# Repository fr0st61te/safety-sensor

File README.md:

# safety-sensor

This is a primitive safety/tamper sensor based on STM8 and VCNL3020 proximity sensor with simple backup power mechanism. STM8 application saves state
of interrupt and store it in flash memory, blinks when interrupt occurs.

# Schematic

# PCB

# Physical examples

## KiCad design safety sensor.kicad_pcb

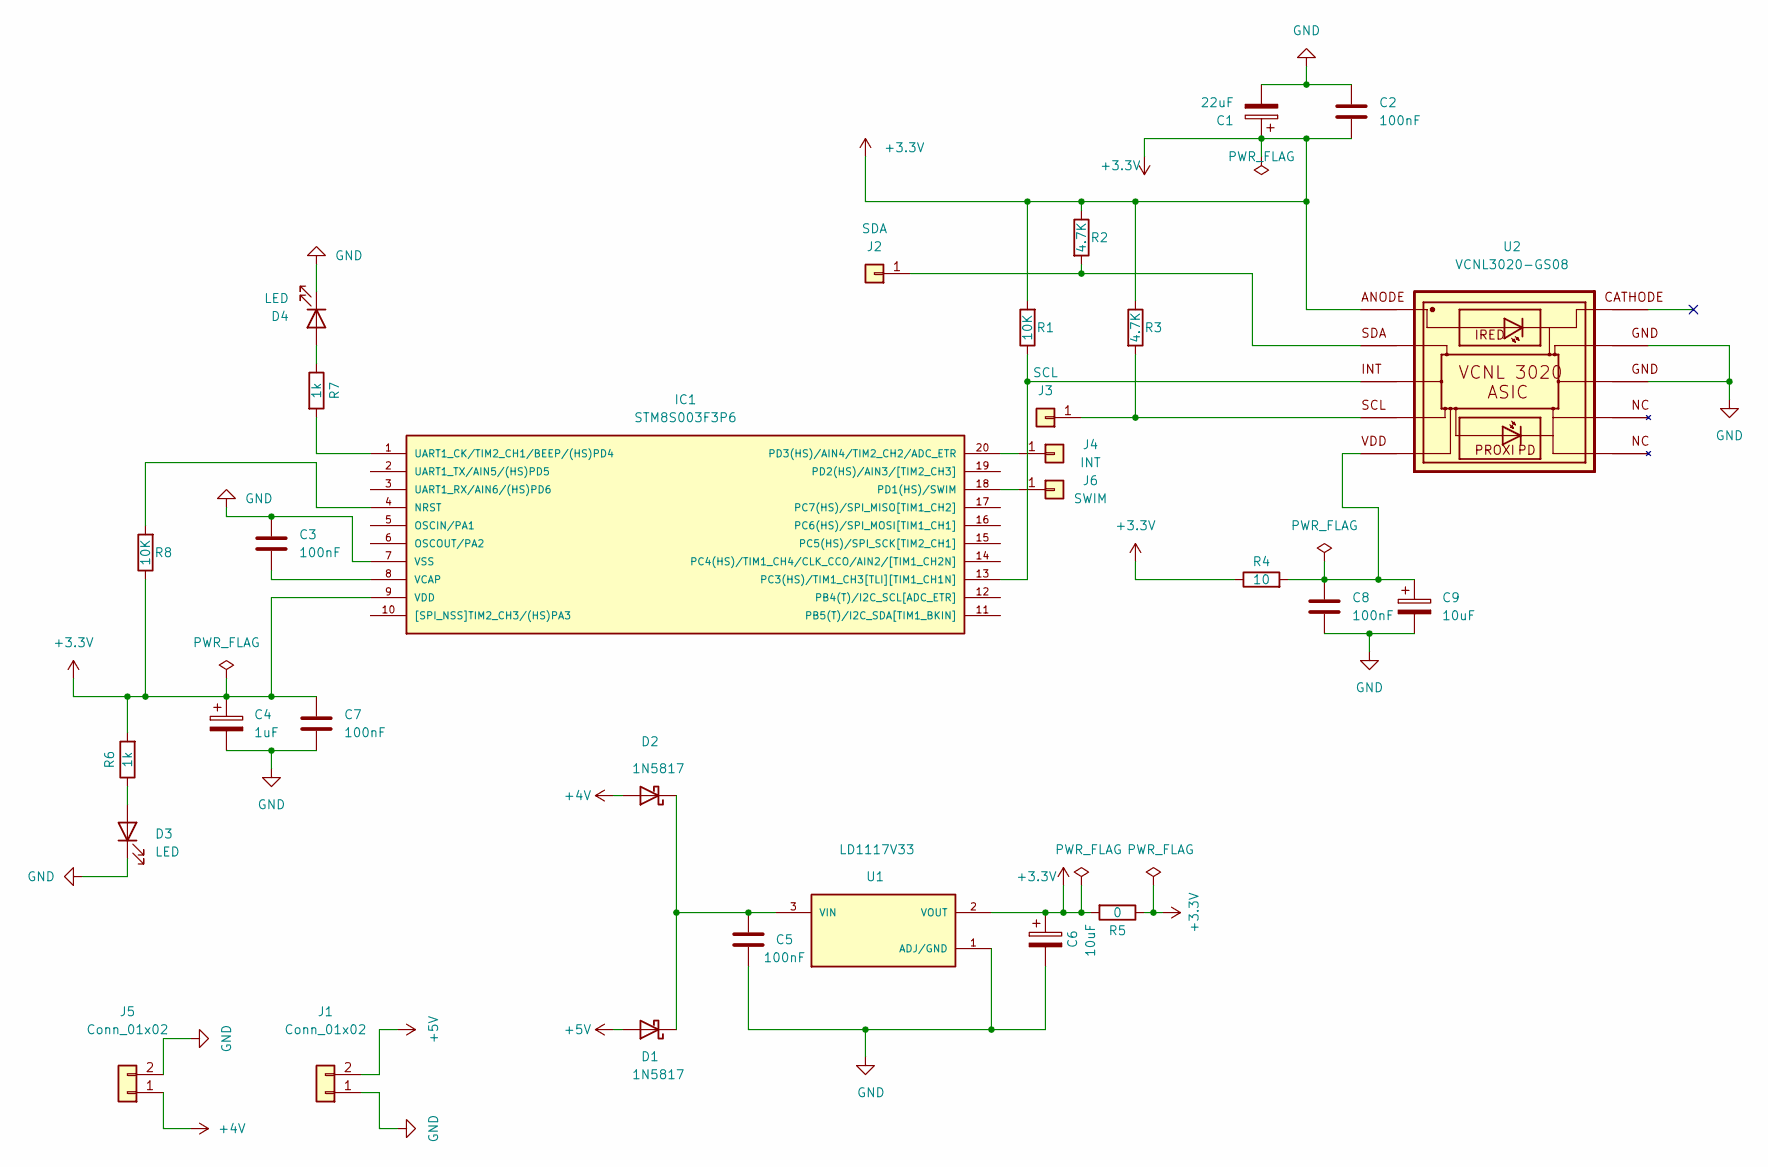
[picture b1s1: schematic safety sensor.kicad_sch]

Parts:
C1: 22uF; CP_Radial_D5.0mm_P2.50mm
C2, C3, C5, C7, C8: 100nF; C_Disc_D3.0mm_W2.0mm_P2.50mm
C4: 1uF; CP_Radial_D5.0mm_P2.50mm
C6, C9: 10uF; CP_Radial_D5.0mm_P2.50mm
D1, D2: 1N5817; D_DO-41_SOD81_P10.16mm_Horizontal
D3, D4: LED; LED_D5.0mm
IC1: STM8S003F3P6; TSSOP20
J1, J5: Conn_01x02; PinHeader_1x02_P2.54mm_Vertical
J2: SDA; PinHeader_1x01_P2.54mm_Vertical
J3: SCL; PinHeader_1x01_P2.54mm_Vertical
J4: INT; PinHeader_1x01_P2.54mm_Vertical
J6: SWIM; PinHeader_1x01_P2.54mm_Vertical
R1, R8: 10K; R_Axial_DIN0207_L6.3mm_D2.5mm_P10.16mm_Horizontal
R2, R3: 4.7K; R_Axial_DIN0207_L6.3mm_D2.5mm_P10.16mm_Horizontal
R4: 10; R_Axial_DIN0207_L6.3mm_D2.5mm_P10.16mm_Horizontal
R5: 0; R_Axial_DIN0207_L6.3mm_D2.5mm_P15.24mm_Horizontal
R6, R7: 1k; R_Axial_DIN0207_L6.3mm_D2.5mm_P10.16mm_Horizontal
U1: LD1117V33; TO255P1020X450X1968-3; PARTREV 37
U2: VCNL3020-GS08; XDCR_VCNL3020-GS08; PARTREV 1.2

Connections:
+3.3V: C1.1, C2.2, C4.1, C6.1, C7.1, IC1.9 (VDD), R1.2, R2.1, R3.1, R4.1, R5.1, R5.2, R6.2, R8.1, U1.2 (VOUT), U2.1
+4V: D2.2 (A), J5.1
+5V: D1.2 (A), J1.2
GND: C1.2, C2.1, C3.1, C4.2, C5.1, C6.2, C7.2, C8.2, C9.2, D3.1 (K), D4.1 (K), IC1.7 (VSS), J1.1, J5.2, U1.1 (ADJ/GND), U2.8, U2.9
unnamed: C3.2, IC1.8 (VCAP)
unnamed: C5.2, D1.1 (K), D2.1 (K), U1.3 (VIN)
unnamed: C8.1, C9.1, R4.2, U2.5
unnamed: D3.2 (A), R6.1
unnamed: D4.2 (A), R7.1
unnamed: IC1.1 (UART1_CK/TIM2_CH1/BEEP/(HS)PD4), R7.2
unnamed: IC1.4 (NRST), R8.2
unnamed: IC1.13 (PC3(HS)/TIM1_CH3[TLI][TIM1_CH1N]), R1.1, U2.3
unnamed: IC1.18 (PD1(HS)/SWIM), J6.1
unnamed: IC1.20 (PD3(HS)/AIN4/TIM2_CH2/ADC_ETR), J4.1
unnamed: J2.1, R2.2, U2.2
unnamed: J3.1, R3.2, U2.4

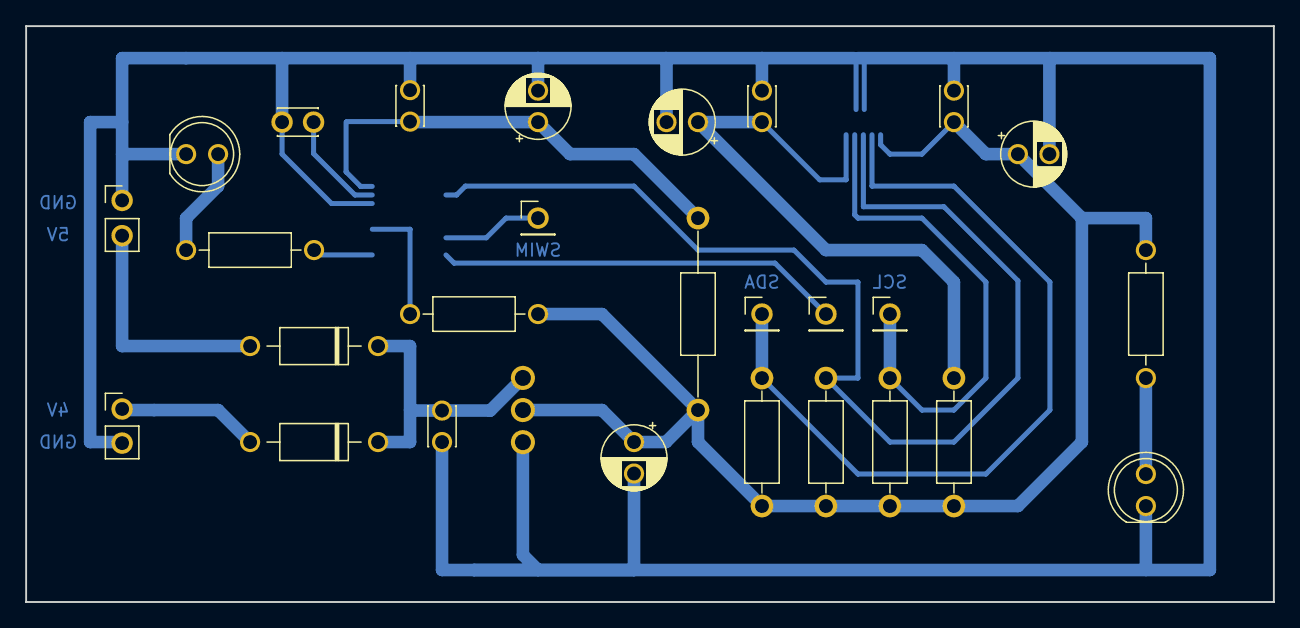
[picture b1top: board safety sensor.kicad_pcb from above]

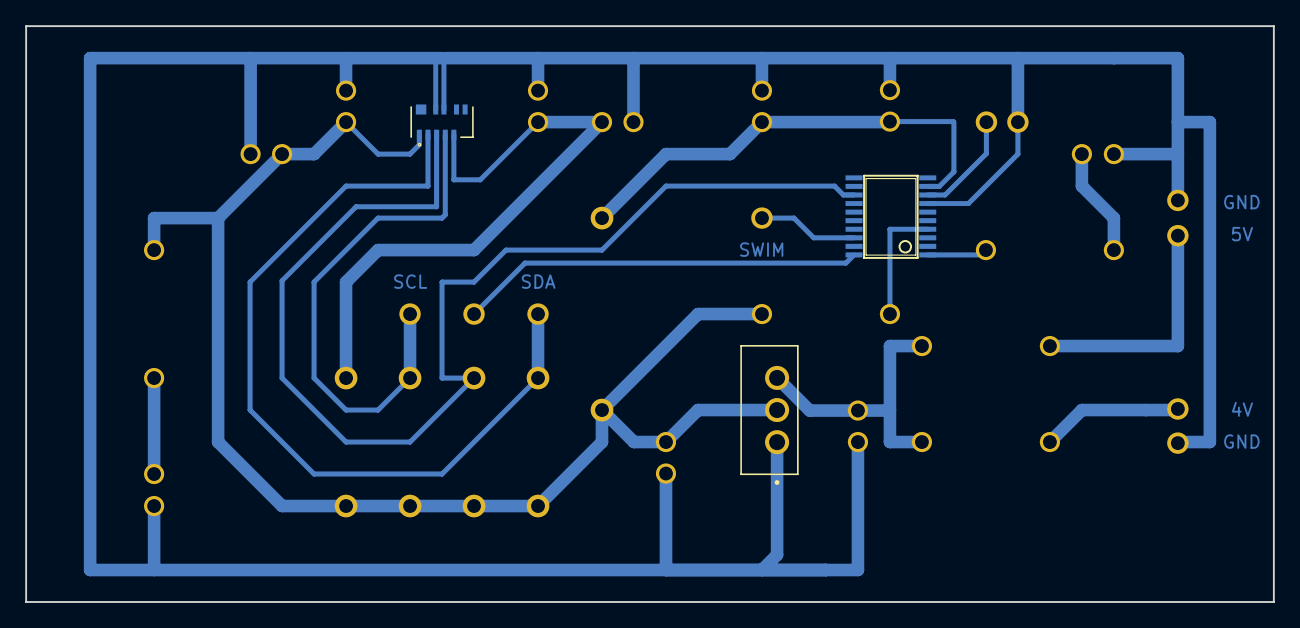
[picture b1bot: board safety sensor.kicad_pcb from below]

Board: 2 copper layers, 99.1 x 45.7 mm, 30 parts (3 on the bottom side), 16 nets.

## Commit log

2022-10-14 add vcnl3020 connector part
    Initial commit with kicad project for vcnl3020 proximity sensor.
2022-10-23 add stm8 microcontroller and ld1117v33 voltage regulator footprints
2022-10-23 add stm8 to the board with connection to interrupt line of vcnl3020
2022-10-23 increase track width and pad size change
2022-10-24 add SWIM connector
2022-10-25 polish schematics, add leds for voltage lines and gpio for stm8
2022-11-08 fix c1 polarity, fix the hole sizes
2022-11-25 change chip leg size on stm8 chip
2022-11-25 flip stm8 chip, update from updated footrpint and connect it accordingly
2022-11-25 fixing track pad connection errors and polishing stm8 tssop20 footprint
2022-11-25 add Makefile for stm8 build lib
    Based on https://gist.github.com/webhive/505c2891b6f3c7a253b29e07575ab34c
2022-11-26 pad name changes in schematic
2022-11-26 flip stm8 side
2022-11-28 add pull up resistor for nrst, change hole size for voltage connectors
2023-01-19 add applications for stm8
2023-06-25 Add additional information about project
